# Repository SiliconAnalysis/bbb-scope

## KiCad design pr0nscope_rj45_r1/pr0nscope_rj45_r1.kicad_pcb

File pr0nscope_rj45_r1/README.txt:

Bom?
pr0nscope BOM
2x DB25
    108-57541
    1634349-1
    1734349
    https://www.digikey.com/products/en/connectors-interconnects/d-sub-connectors/439?k=1734349&k=&pkeyword=1734349&quantity=0&ColumnSort=0&page=1&stock=1&pageSize=25
        obsolete item
        qty 3
        hmm did I choose poorly?
        oh well, buy the stock
1x 7805
    https://www.digikey.com/product-detail/en/texas-instruments/LM7805MPX-NOPB/296-44518-1-ND/6110827
phoenix connector
    https://www.digikey.com/product-detail/en/phoenix-contact/1776508/277-5741-ND/349000
2x RJ45
    FCI / Amphenol : 54602-908LF
    rj45_c-bmj-0102-1365276.pdf
2x LED step
    blue?
2x LED dir
    green?
1x LED power
    green?
misc resistors
    use stock
case
    https://www.digikey.com/product-detail/en/hammond-manufacturing/1455R1601BK/HM1738-ND/2360649
    1455R1602BK
        aluminum ends non-stock

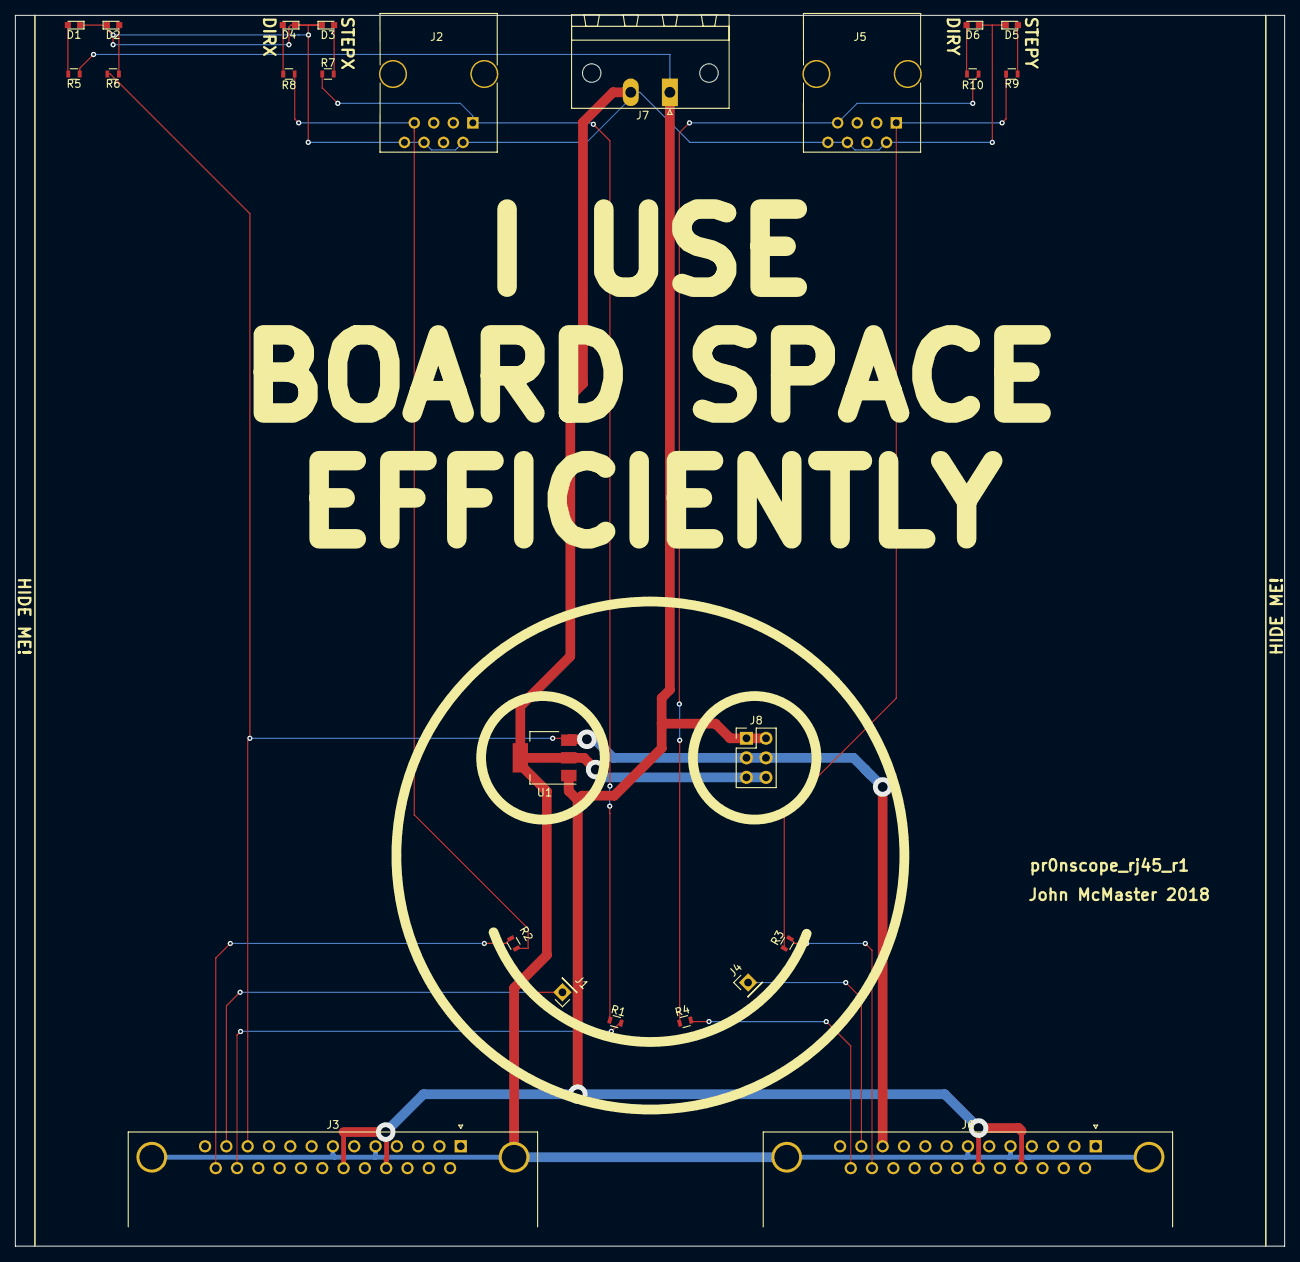
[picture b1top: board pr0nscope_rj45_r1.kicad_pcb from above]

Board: 2 copper layers, 165.0 x 160.0 mm, 25 parts (0 on the bottom side), 19 nets.

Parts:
D1, D2, D3, D4, D5, D6: LED; LED_0603
J1, J4: Conn_01x01; Pin_Header_Straight_1x01_Pitch2.54mm
J2, J5: RJ45-index; RJ45_8
J3, J6: pr0nscope_db25f_gnd; DSUB-25_Female_Horizontal_Pitch2.77x2.84mm_EdgePinOffset7.7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
J7: Conn_01x02; PhoenixContact_MSTB-GF_02x5.08mm_Angled_ThreadedFlange_Moun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
J8: Conn_02x03_Odd_Even; Pin_Header_Straight_2x03_Pitch2.54mm
R1, R2, R3, R4: 0; R_0603
R5, R6, R7, R8, R9, R10: R; R_0603
U1: L7805; SOT-223-3_TabPin2

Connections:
+5V: J3.11, J6.11, J8.3, J8.4, R6.1, U1.3
GND: D1.1, D2.1, D3.1, D4.1, D5.1, D6.1, J2.2, J2.6, J2.8, J3.0, J3.5, J3.7, J5.2, J5.6, J5.8, J6.0, J6.5, J6.7, J7.2, J8.5, J8.6, U1.2
unnamed: D1.2, R5.2
unnamed: D2.2, R6.2
unnamed: D3.2, R7.2
unnamed: D4.2, R8.2
unnamed: D5.2, R9.2
unnamed: D6.2, R10.2
unnamed: J1.1, J3.12
unnamed: J2.1, R1.1, R7.1
unnamed: J2.7, R2.1, R8.1
unnamed: J3.24, R1.2
unnamed: J3.25, R2.2
unnamed: J4.1, J6.12
unnamed: J5.1, R3.1, R9.1
unnamed: J5.7, R4.1, R10.1
unnamed: J6.24, R3.2
unnamed: J6.25, R4.2
VDD: J3.17, J3.19, J6.17, J6.19, J7.1, J8.1, J8.2, R5.1, U1.1

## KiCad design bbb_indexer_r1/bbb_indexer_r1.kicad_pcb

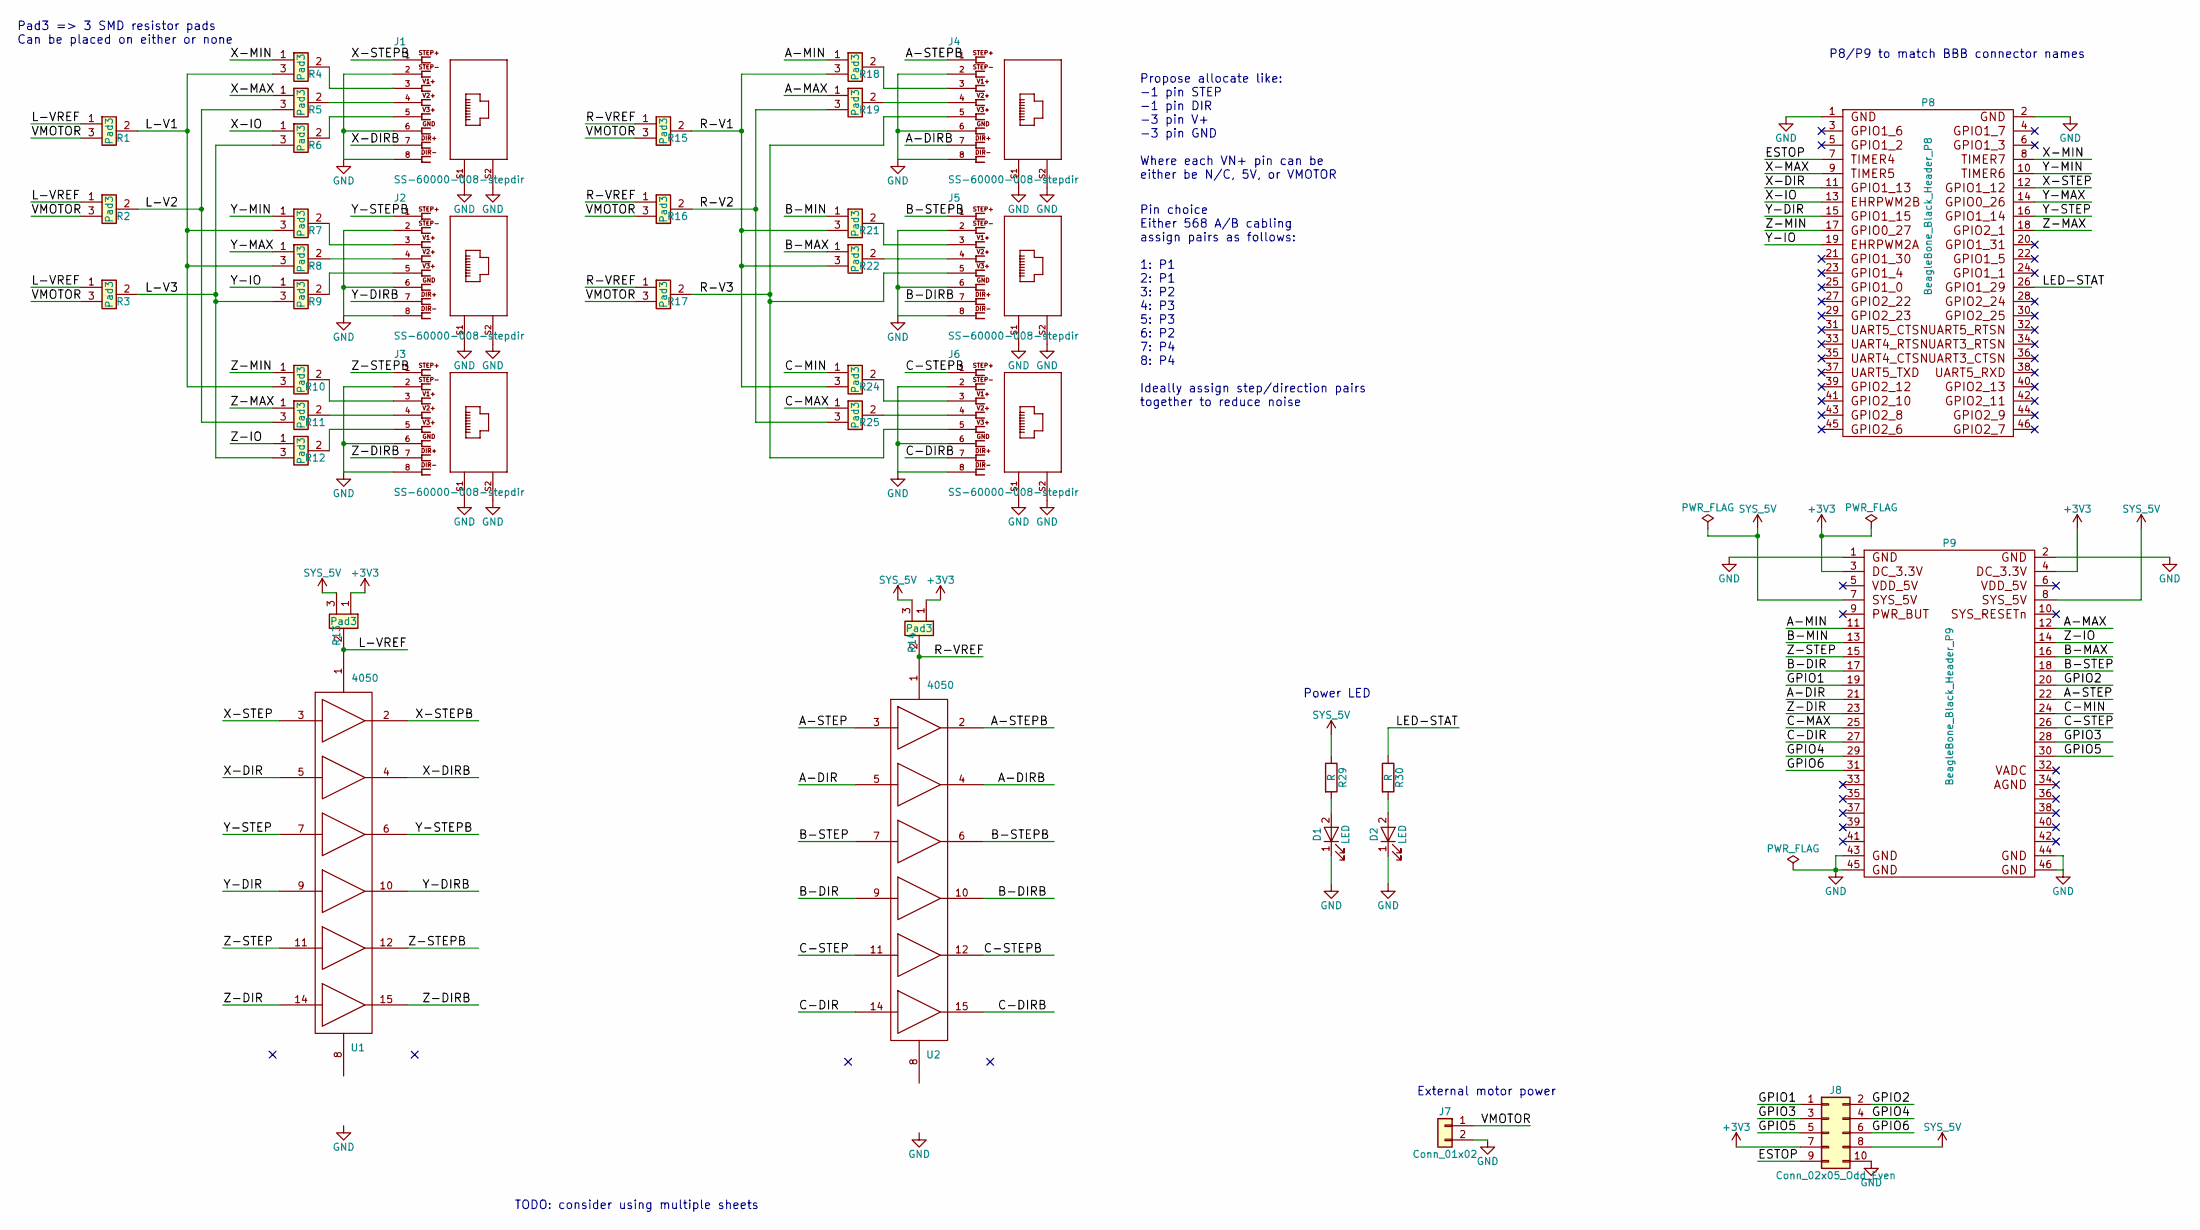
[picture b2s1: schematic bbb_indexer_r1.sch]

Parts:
D1, D2: LED; LED_0603
J1, J2, J3, J4, J5, J6: SS-60000-008-stepdir; 520260-4
J7: Conn_01x02; Pin_Header_Straight_1x02_Pitch2.54mm
J8: Conn_02x05_Odd_Even; Pin_Header_Straight_2x05_Pitch2.54mm
P8: BeagleBone_Black_Header_P8; Socket_BeagleBone_Black
P9: BeagleBone_Black_Header_P9; Socket_BeagleBone_Black
R1, R2, R3, R4, R5, R6, R7, R8, R9, R10, R11, R12, R13, R14, R15, R16, R17, R18, R19, R21, R22, R24, R25: Pad3; R3_0603
R29, R30: R; R_0603
U1, U2: 4050; SOIC-16_3.9x9.9mm_Pitch1.27mm

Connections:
+3V3: J8.7, P9.3, P9.4, R13.1, R14.1
/A-DIR: P9.21, U2.5
/A-DIRB: J4.7, U2.4
/A-MAX: P9.12, R19.1
/A-MIN: P9.11, R18.1
/A-STEP: P9.22, U2.3
/A-STEPB: J4.1, U2.2
/B-DIR: P9.17, U2.9
/B-DIRB: J5.7, U2.10
/B-MAX: P9.16, R22.1
/B-MIN: P9.13, R21.1
/B-STEP: P9.18, U2.7
/B-STEPB: J5.1, U2.6
/C-DIR: P9.27, U2.14
/C-DIRB: J6.7, U2.15
/C-MAX: P9.25, R25.1
/C-MIN: P9.24, R24.1
/C-STEP: P9.26, U2.11
/C-STEPB: J6.1, U2.12
/ESTOP: J8.9, P8.7
/GPIO1: J8.1, P9.19
/GPIO2: J8.2, P9.20
/GPIO3: J8.3, P9.28
/GPIO4: J8.4, P9.29
/GPIO5: J8.5, P9.30
/GPIO6: J8.6, P9.31
/L-V1: R1.2, R4.3, R7.3, R8.3, R10.3
/L-V2: R2.2, R5.3, R11.3
/L-V3: R3.2, R6.3, R9.3, R12.3
/L-VREF: R1.1, R2.1, R3.1, R13.2, U1.1
/LED-STAT: P8.26, R30.1
/R-V1: R15.2, R18.3, R21.3, R22.3, R24.3
/R-V2: R16.2, R19.3, R25.3
/R-V3: J4.5, J5.5, J6.5, R17.2
/R-VREF: R14.2, R15.1, R16.1, R17.1, U2.1
/VMOTOR: J7.1, R1.3, R2.3, R3.3, R15.3, R16.3, R17.3
/X-DIR: P8.11, U1.5
/X-DIRB: J1.7, U1.4
/X-IO: P8.13, R6.1
/X-MAX: P8.9, R5.1
/X-MIN: P8.8, R4.1
/X-STEP: P8.12, U1.3
/X-STEPB: J1.1, U1.2
/Y-DIR: P8.15, U1.9
/Y-DIRB: J2.7, U1.10
/Y-IO: P8.19, R9.1
/Y-MAX: P8.14, R8.1
/Y-MIN: P8.10, R7.1
/Y-STEP: P8.16, U1.7
/Y-STEPB: J2.1, U1.6
/Z-DIR: P9.23, U1.14
/Z-DIRB: J3.7, U1.15
/Z-IO: P9.14, R12.1
/Z-MAX: P8.18, R11.1
/Z-MIN: P8.17, R10.1
/Z-STEP: P9.15, U1.11
/Z-STEPB: J3.1, U1.12
GND: D1.1 (K), D2.1 (K), J1.2, J1.6, J1.8, J1.S1, J1.S2, J2.2, J2.6, J2.8, J2.S1, J2.S2, J3.2, J3.6, J3.8, J3.S1, J3.S2, J4.2, J4.6, J4.8, J4.S1, J4.S2, J5.2, J5.6, J5.8, J5.S1, J5.S2, J6.2, J6.6, J6.8, J6.S1, J6.S2, J7.2, J8.10, P8.1, P8.2, P9.1, P9.2, P9.43, P9.44, P9.45, P9.46, U1.8, U2.8
unnamed: D1.2 (A), R29.2
unnamed: D2.2 (A), R30.2
unnamed: J1.3, R4.2
unnamed: J1.4, R5.2
unnamed: J1.5, R6.2
unnamed: J2.3, R7.2
unnamed: J2.4, R8.2
unnamed: J2.5, R9.2
unnamed: J3.3, R10.2
unnamed: J3.4, R11.2
unnamed: J3.5, R12.2
unnamed: J4.3, R18.2
unnamed: J4.4, R19.2
unnamed: J5.3, R21.2
unnamed: J5.4, R22.2
unnamed: J6.3, R24.2
unnamed: J6.4, R25.2
SYS_5V: J8.8, P9.7, P9.8, R13.3, R14.3, R29.1

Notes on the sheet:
Pin choice Either 568 A/B cabling assign pairs as follows: 1: P1 2: P1 3: P2 4: P3 5: P3 6: P2 7: P4 8: P4 Ideally assign step/direction pairs together to reduce noise
Propose allocate like: -1 pin STEP -1 pin DIR -3 pin V+ -3 pin GND Where each VN+ pin can be either be N/C, 5V, or VMOTOR
P8/P9 to match BBB connector names
Power LED
External motor power
Pad3 => 3 SMD resistor pads Can be placed on either or none
TODO: consider using multiple sheets

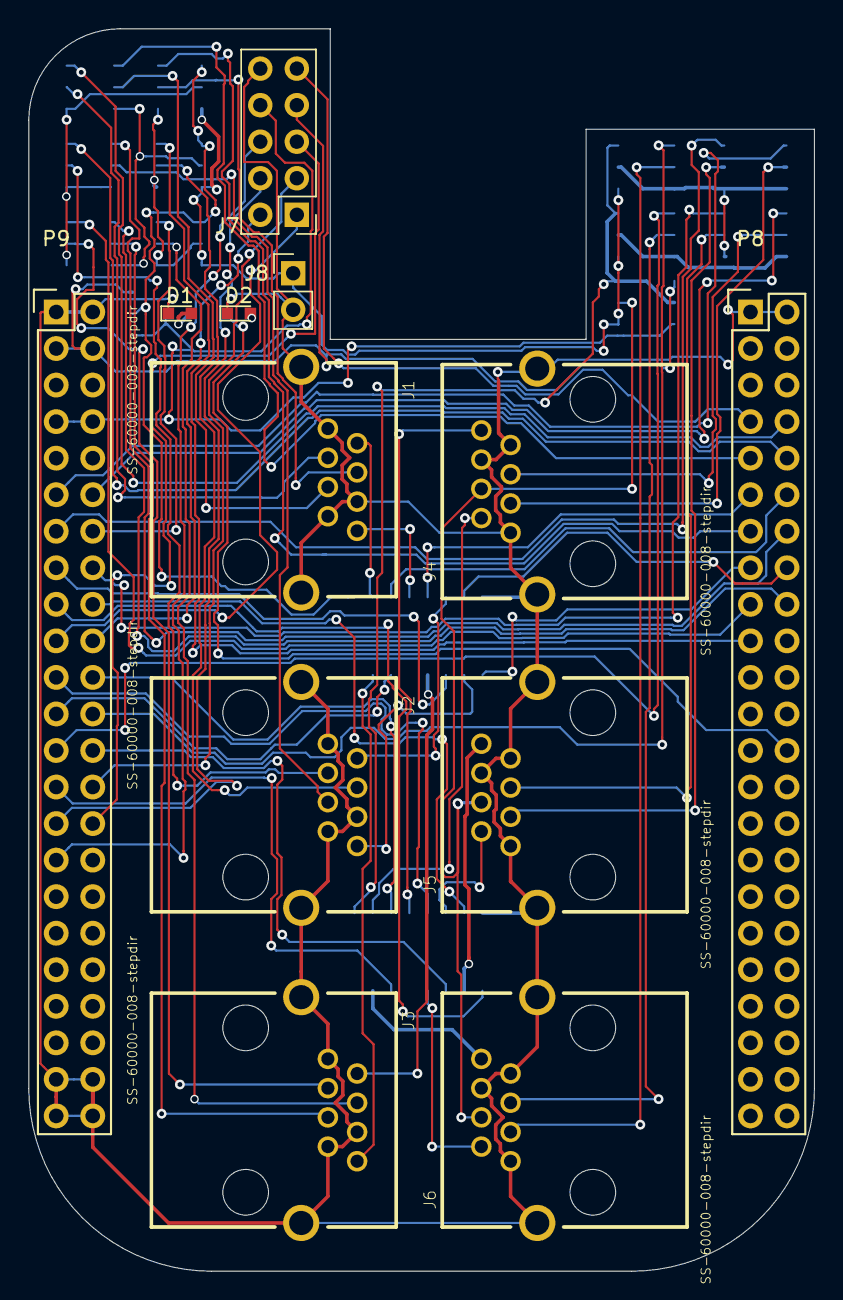
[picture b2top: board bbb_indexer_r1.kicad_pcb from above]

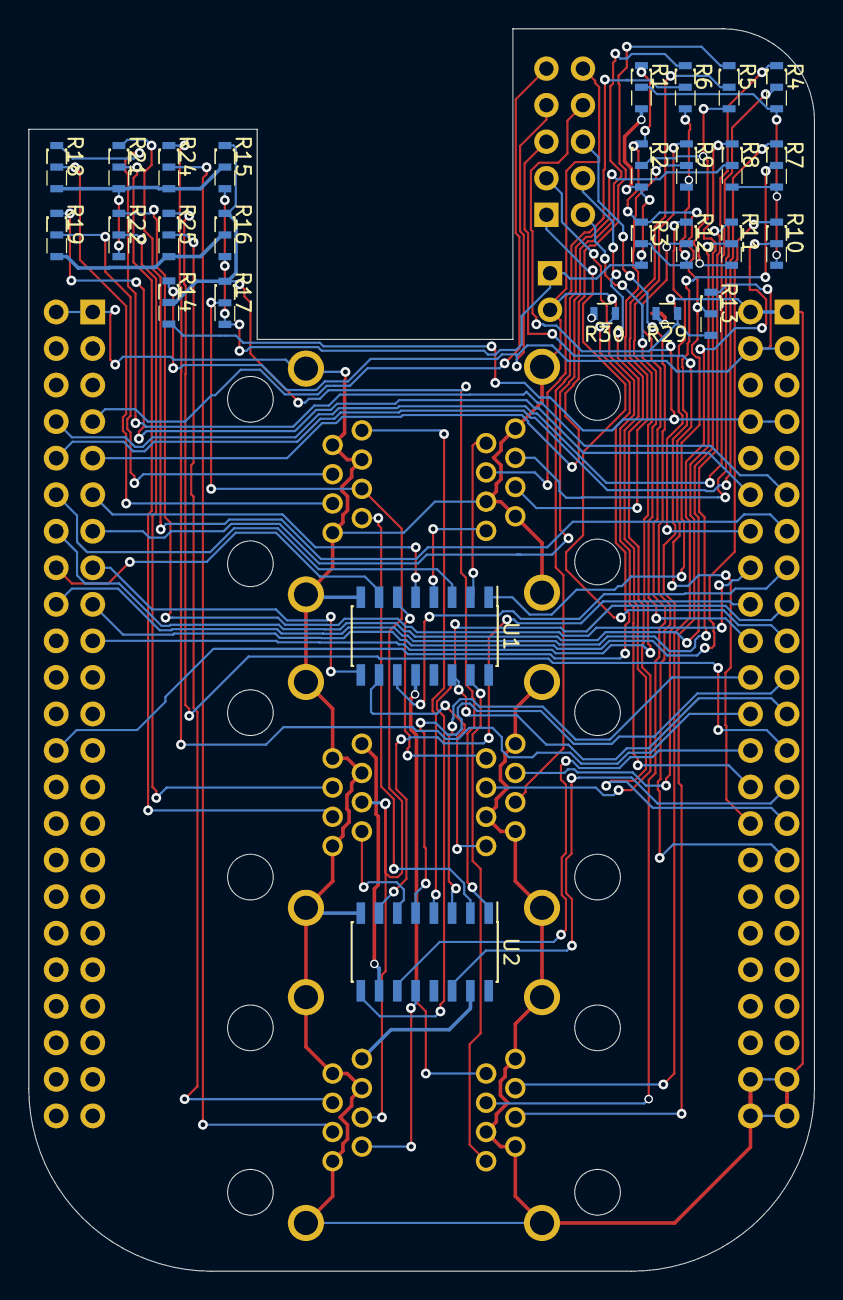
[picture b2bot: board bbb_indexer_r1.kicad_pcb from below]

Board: 2 copper layers, 54.6 x 86.4 mm, 39 parts (27 on the bottom side), 76 nets.

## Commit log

2018-05-31 WIP needing lots of library / path cleanup
2018-05-31 remove abaondoned project files
2018-05-31 Rename bbb-cape => bbb_indexer_r1
2018-05-31 Rename project files BeagleBone-Black-Cape => bbb_indexer_r1
2018-05-31 Shuffle library files
2018-05-31 Remove unused cd4000 library
2018-05-31 Remove test libraries
2018-05-31 Flatten cd4050 library a little
2018-05-31 Remove unused connector library
2018-05-31 Flatten SS-60000-008 library
2018-05-31 Flatten BBB lib
2018-05-31 Move BBB cape into own library from cache
2018-05-31 Add lib README
2018-06-01 Design using GPIO much more exhaustively
2018-06-01 Schematic RC complete
2018-06-01 routing mostly complete
2018-06-01 Fully routed, DRC passes
2018-06-01 Small silkscreen cleanup
2018-06-02 bbb_indexer_r1-rc5 I think
2018-06-02 b3index_r1 rename
2018-06-02 b3index_r1 production zip
2018-06-02 pr0nscope adapter
2018-06-03 pr0nscope_rj45_r1_rc1
2018-06-05 pr0nscope_rj45_r1 rc2: increase power via size
2018-06-12 b3index_r1 documentation
2018-06-15 pr0nscope_rj45_r1: add BOM info
2019-08-12 add schematic pdf
2019-08-12 add rest of release
